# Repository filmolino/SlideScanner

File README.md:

# Filmolino SlideScanner
The Filmolino SlideScanner is a device that makes it easy to scan slides in magazines fully automated using a modified slide projector and a digital camera. It controls the slide projector and a digital camera using a cable release or an infrared remote control (Nikon, Canon, Pentax, Sony, Olympus, Minolta). New cable releases and IR controls can easyily be added to the software. 
 
Thanks to the [M5StampC3 from M5Stack](https://shop.m5stack.com/collections/m5-controllers/products/fire-iot-development-kit) using a ESP-32 core together with 16M Flash, 8M PSRAM and a built in 3.7V/500mAh Lithium battery it is also possible to use the device without a power supply and remote control the SlideScanner through a web interface over WiFi. The scanner has it's own access point to which you can connect.

The Filmolino SlideScanner is completely open source, so you can easy build your own!

For more info about the project please visit [Filmolino SlideScanner](https://filmolino.com/slidescanner/)

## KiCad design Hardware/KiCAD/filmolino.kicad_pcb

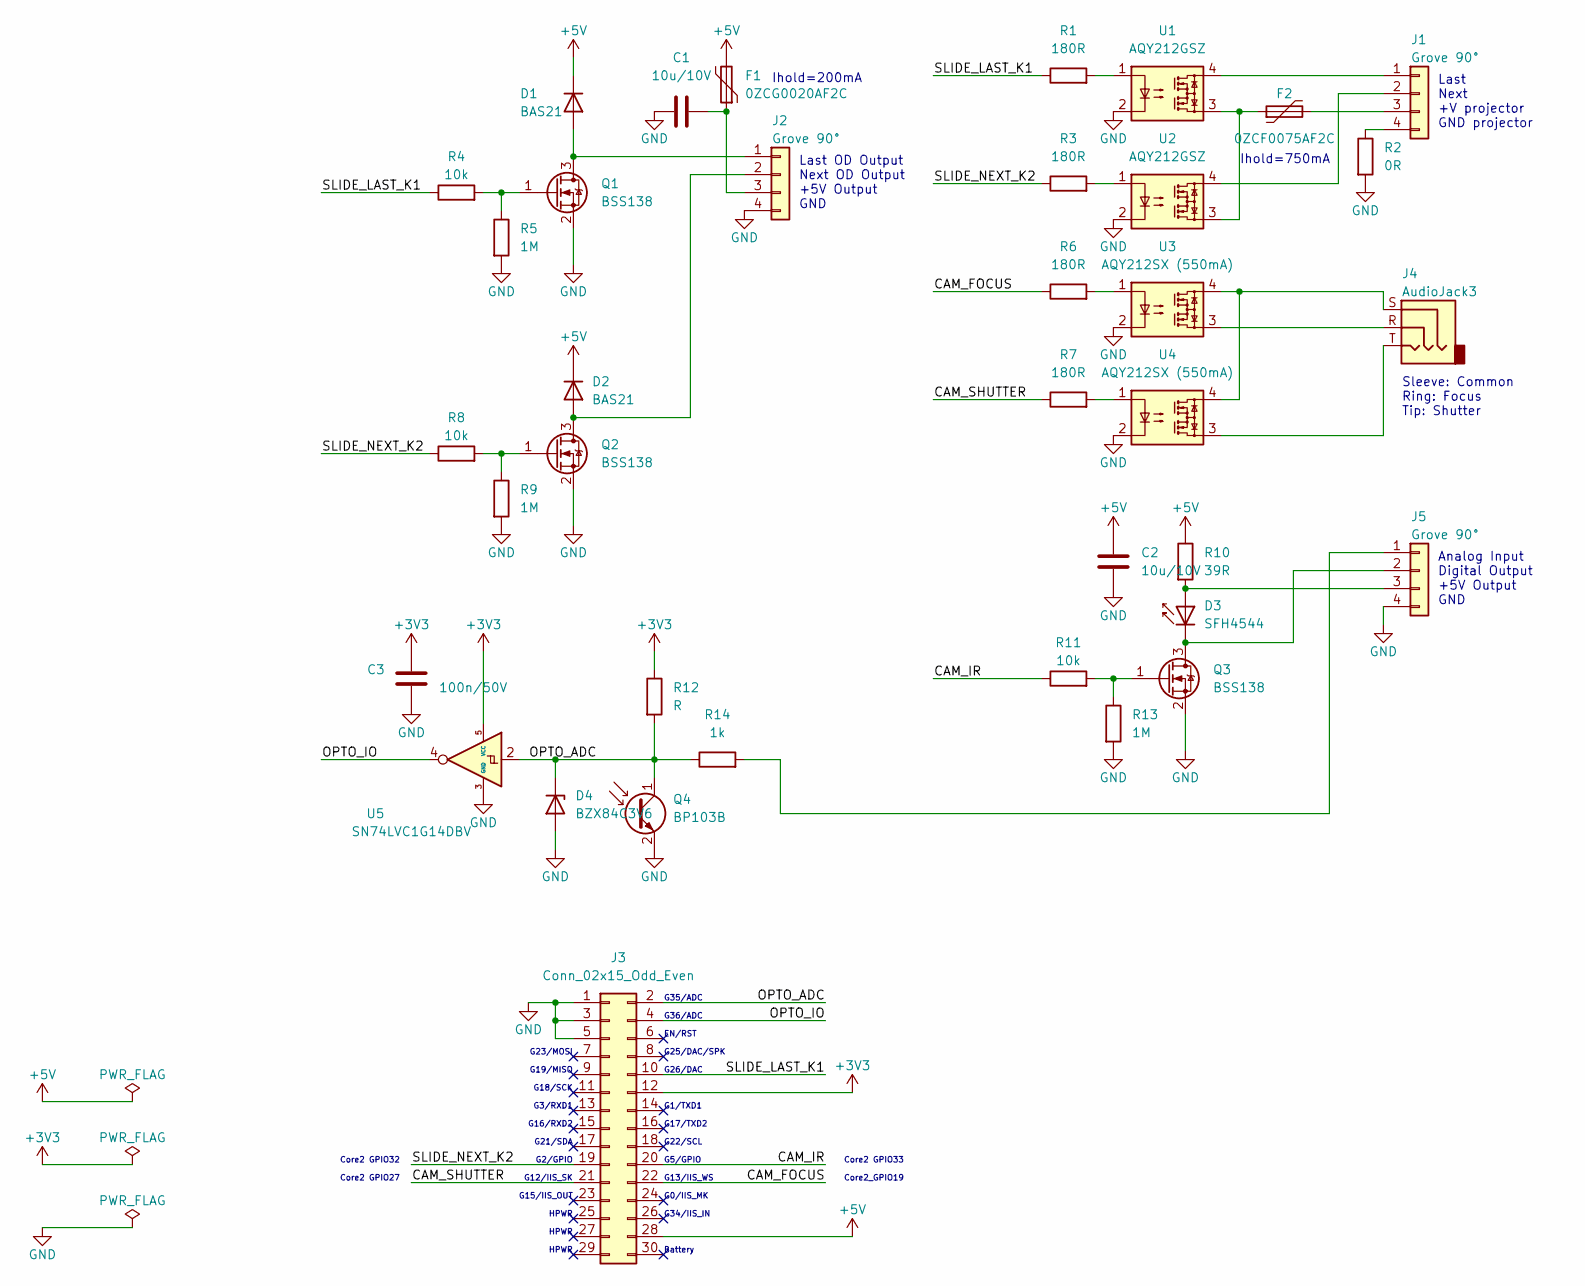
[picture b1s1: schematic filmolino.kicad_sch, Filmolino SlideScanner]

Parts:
C1, C2: 10u/10V; C_0805_2012Metric_Pad1.18x1.45mm_HandSolder
C3: 100n/50V; C_0805_2012Metric_Pad1.18x1.45mm_HandSolder
D1, D2: BAS21; SOT-23
D3: SFH4544; LED_D5.0mm_Horizontal_O1.27mm_Z3.0mm
D4: BZX84C3V6; SOT-23
F1: 0ZCG0020AF2C; BelFuse_0ZCG_Metric_Pad1.78x3.50mm
F2: 0ZCF0075AF2C; BelFuse_0ZCF_Metric_Pad2.30x5.60mm
J1, J2, J5: Grove 90°; Grove_Con_1x04_2mm_horizontal
J3: Conn_02x15_Odd_Even; PinHeader_2x15_P2.54mm_Holes0.75mm_Vertical
J4: AudioJack3; Jack_2.5mm_Lumberg_1501_04
Q1, Q2, Q3: BSS138; SOT-23
Q4: BP103B; LED_D5.0mm_Horizontal_O1.27mm_Z3.0mm
R1, R3, R6, R7: 180R; R_0805_2012Metric_Pad1.20x1.40mm_HandSolder
R2: 0R; R_0805_2012Metric_Pad1.20x1.40mm_HandSolder
R4, R8, R11: 10k; R_0805_2012Metric_Pad1.20x1.40mm_HandSolder
R5, R9, R13: 1M; R_0805_2012Metric_Pad1.20x1.40mm_HandSolder
R10: 39R; R_1206_3216Metric_Pad1.30x1.75mm_HandSolder
R12: R; R_0805_2012Metric_Pad1.20x1.40mm_HandSolder
R14: 1k; R_1206_3216Metric_Pad1.30x1.75mm_HandSolder
U1, U2: AQY212GSZ; SOP-4_4.4x4.3mm_P2.54mm
U3, U4: AQY212SX (550mA); SOP-4_4.4x4.3mm_P2.54mm
U5: SN74LVC1G14DBV; SOT-23-5

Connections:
+3V3: C3.1, J3.12, R12.1, U5.5 (VCC)
+5V: C2.1, D1.3 (K), D2.3 (K), F1.2, J3.28, R10.1
/CAM_FOCUS: J3.22, R6.1
/CAM_IR: J3.20, R11.1
/CAM_SHUTTER: J3.21, R7.1
/OPTO_ADC: D4.3 (K), J3.2, Q4.1 (C), R12.2, R14.1, U5.2
/OPTO_IO: J3.4, U5.4
/SLIDE_LAST_K1: J3.10, R1.1, R4.1
/SLIDE_NEXT_K2: J3.19, R3.1, R8.1
GND: C1.2, C2.2, C3.2, D4.1 (A), J2.4, J3.1, J3.3, J3.5, J5.4, Q1.2 (S), Q2.2 (S), Q3.2 (S), Q4.2 (E), R2.2, R5.2, R9.2, R13.2, U1.2, U2.2, U3.2, U4.2, U5.3 (GND)
unnamed: C1.1, F1.1, J2.3
unnamed: D1.1 (A), J2.1, Q1.3 (D)
unnamed: D2.1 (A), J2.2, Q2.3 (D)
unnamed: D3.1 (K), J5.2, Q3.3 (D)
unnamed: D3.2 (A), J5.3, R10.2
unnamed: F2.1, U1.3, U2.3
unnamed: F2.2, J1.3
unnamed: J1.1, U1.4
unnamed: J1.2, U2.4
unnamed: J1.4, R2.1
unnamed: J4.R, U3.3
unnamed: J4.S, U3.4, U4.4
unnamed: J4.T, U4.3
unnamed: J5.1, R14.2
unnamed: Q1.1 (G), R4.2, R5.1
unnamed: Q2.1 (G), R8.2, R9.1
unnamed: Q3.1 (G), R11.2, R13.1
unnamed: R1.2, U1.1
unnamed: R3.2, U2.1
unnamed: R6.2, U3.1
unnamed: R7.2, U4.1

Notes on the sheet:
Core2 GPIO27
Ihold=750mA
G3/RXD1
Last OD Output Next OD Output +5V Output GND
EN/RST
G16/RXD2
G12/IIS_SK
G36/ADC
HPWR
Battery
G17/TXD2
G22/SCL
Sleeve: Common Ring: Focus Tip: Shutter
Core2 GPIO33
G35/ADC
G18/SCK
Last Next +V projector GND projector
Ihold=200mA
G23/MOSI
G26/DAC
G1/TXD1
G13/IIS_WS
G19/MISO
Core2 GPIO32
G15/IIS_OUT
G0/IIS_MK
G25/DAC/SPK
G34/IIS_IN
Analog Input Digital Output +5V Output GND
G5/GPIO
G2/GPIO
G21/SDA
Core2_GPIO19

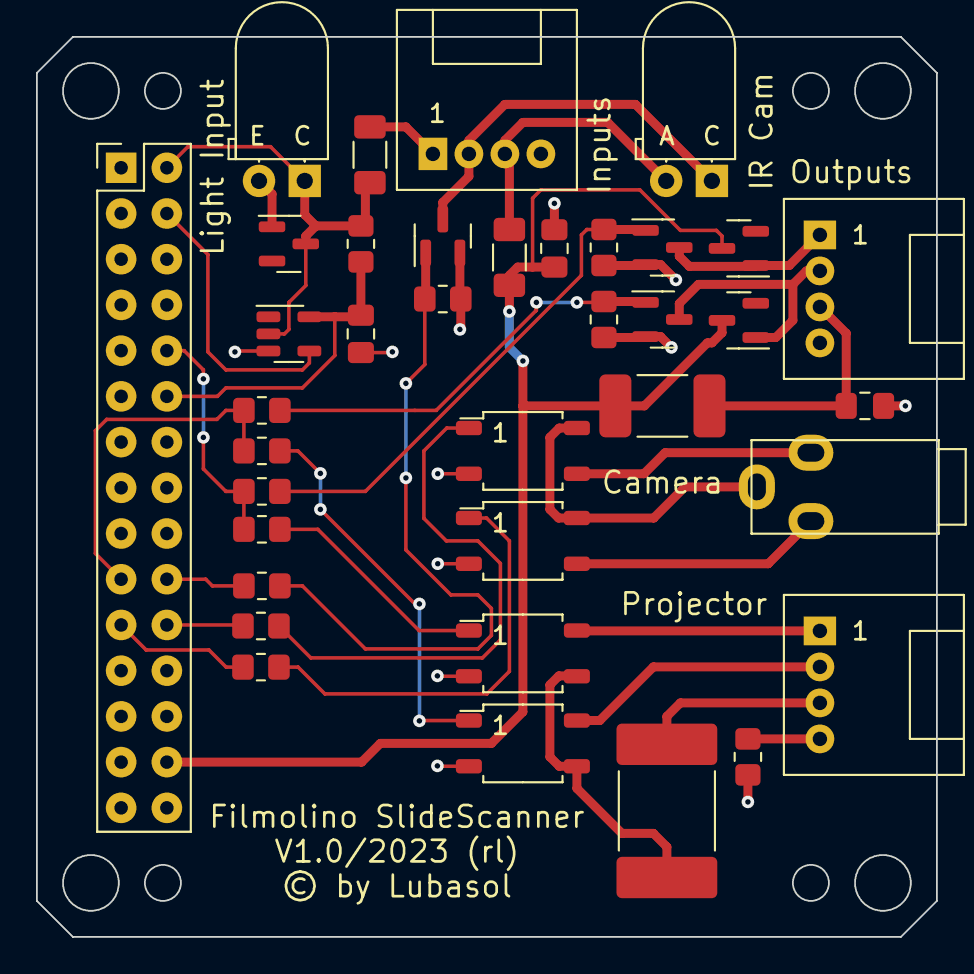
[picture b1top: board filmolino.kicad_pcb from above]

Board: 2 copper layers, 50.0 x 50.0 mm, 37 parts (0 on the bottom side), 31 nets.

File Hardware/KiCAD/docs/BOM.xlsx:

Id | Designator | Package | Quantity | Designation | Supplier and ref
1 | Q3,Q1,Q2 | SOT-23 | 3 | BSS138
2 | D1,D2 | SOT-23 | 2 | BAS21
3 | U3,U4 | SOP-4_4.4x4.3mm_P2.54mm | 2 | AQY212SX (550mA)
4 | U2,U1 | SOP-4_4.4x4.3mm_P2.54mm | 2 | AQY212GSZ
5 | R9,R5,R13 | R_0805_2012Metric_Pad1.20x1.40mm_HandSolder | 3 | 1M
6 | F1 | BelFuse_0ZCG_Metric_Pad1.78x3.50mm | 1 | 0ZCG0020AF2C
7 | R12 | R_0805_2012Metric_Pad1.20x1.40mm_HandSolder | 1 | R
8 | J4 | Jack_2.5mm_Lumberg_1501_04 | 1 | AudioJack3
9 | D4 | SOT-23 | 1 | BZX84C3V6
10 | J2,J1,J5 | Grove_Con_1x04_2mm_horizontal | 3 | Grove 90Â°
11 | J3 | PinHeader_2x15_P2.54mm_Holes0.75mm_Vertical | 1 | Conn_02x15_Odd_Even
12 | U5 | SOT-23-5 | 1 | SN74LVC1G14DBV
13 | R4,R11,R8 | R_0805_2012Metric_Pad1.20x1.40mm_HandSolder | 3 | 10k
14 | C2,C1 | C_0805_2012Metric_Pad1.18x1.45mm_HandSolder | 2 | 10u/10V
15 | D3 | LED_D5.0mm_Horizontal_O1.27mm_Z3.0mm | 1 | SFH4544
16 | F2 | BelFuse_0ZCF_Metric_Pad2.30x5.60mm | 1 | 0ZCF0075AF2C
17 | R1,R7,R3,R6 | R_0805_2012Metric_Pad1.20x1.40mm_HandSolder | 4 | 180R
18 | R2 | R_0805_2012Metric_Pad1.20x1.40mm_HandSolder | 1 | 0R
19 | Q4 | LED_D5.0mm_Horizontal_O1.27mm_Z3.0mm | 1 | BP103B
20 | C3 | C_0805_2012Metric_Pad1.18x1.45mm_HandSolder | 1 | 100n/50V
21 | R14 | R_1206_3216Metric_Pad1.30x1.75mm_HandSolder | 1 | 1k
22 | R10 | R_1206_3216Metric_Pad1.30x1.75mm_HandSolder | 1 | 39R

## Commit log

2023-04-16 First Release
2023-05-01 Update filmolino.kicad_sch
    PCB thichkness and M5Stack module frame added.
2023-05-01 Update filmolino.kicad_sch
    Schematic style corrections.

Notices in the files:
Hardware/KiCAD/filmolino.kicad_pcb:
© by Lubasol
